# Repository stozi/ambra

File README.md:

# Ambra
A [Kalmar](https://github.com/aroum/kalmar)/[A. Dux](https://github.com/tapioki/cephalopoda/tree/main/Architeuthis%20dux)-based 34-key split ortho keyboard. [ZMK shield](https://github.com/stozi/zmk-keyboard-ambra)

### Included from Kalmar

- power switch
- reset button
- solder jumpers to mount the MCU the same way on both sides
- perforations on the tab for the connector between the right & left boards

### Changes from Kalmar

- thumb keys mount at 90° with pogo pins and 3D-printed magnet brackets
- besides Kailh Choc, support for Gateron KS-33, both hotswap only
- JST PH battery connector
- Switched the TRRS jack to the same pogo pin connector used for the thumb keys to prevent shorting (VCC/power is the middle pin so mounting one side backwards won't cause damage)
- ground plane for some ESD protection, new pinout

If you don't need fold-down packability or can't get the magnets, you can run a 9mm or longer M2 bolt through both brackets. However, any fall will then be more likely to cause damage.

Consider putting a non-conductive coating between the JST connector's mount points and the battery. Remove remnants of perforations on the thumb-key board before attaching the bracket. Personally, I solder the top-side jumpers to mount the MCUs component-side up so I can see the LEDs, and keep them safe under a case handcrafted from plumbing silicone.

Passed basic testing.

## BOM

Item     | Qty   | Notes 
----------|-------|-------
[SuperMini NRF52840 MCU](https://www.aliexpress.com/item/1005008099333183.html) | 2 | inc. sockets. Alternatively, ProMicro/Elite-C for a wired build
[Kailh Choc V1](https://a.aliexpress.com/_EGNqHgc) | 34 | key switches. Alternatively, [Gateron KS-33](https://a.aliexpress.com/_EuUuYVU)
[Choc hotswap sockets](https://a.aliexpress.com/_Eu2JK5E) | 34 | Alternatively, [Gateron KS-33 hotswap sockets](https://a.aliexpress.com/_EGlN42e)
[Keycaps](https://a.aliexpress.com/_EGNqLfE) | 34 | 1U. If using KS-33 switches, STL files are provided to print your own 'MX stem, Choc-1U-spaced' caps
[Magnets](https://a.aliexpress.com/_EGMQ442) | 2 | D6×3mm annular cylinder
[RTLECS MG03254 3-pin](https://a.aliexpress.com/_Ev5QIZa) | 2 straight m, 2 90° f | magnetic pogo-pin connectors
[MSK-12CO2](https://aliexpress.ru/item/1005001398386692.html) | 2 | power switch
[SMD button 3×4×2](https://aliexpress.ru/item/1005003812819985.html) | 2 | reset switch
[301230 li-po](https://aliexpress.ru/item/32732458079.html) | 2 | battery
[JST PH right-angle 2-pin](https://www.aliexpress.com/item/1005008131930144.html) | 2 | battery connector
[JST wire](https://www.aliexpress.com/item/1005001649158434.html) | 2 | solder & shrink tube to battery wires, no crimping needed, or [battery already with connector](https://a.aliexpress.com/_EJkhjGm) 
[M3 machine screws, 3mm](https://www.aliexpress.com/item/1005006662972635.html) | 2 | flathead, couples with magnet
[M3 thin hex nuts](https://a.aliexpress.com/_EvCkuwM) | 2 |
[M2 tapered head machine screws, 7mm](https://a.aliexpress.com/_EzeQ9lA) | 2 | holds magnet
[M2 flat head machine screws, 8mm](https://www.aliexpress.com/item/1005006662972635.html) | 6 | for brackets
[M2 thin hex nuts](https://a.aliexpress.com/_EvCkuwM) | 8 |
OPTIONAL: [RTLECS MG03254 cable](https://www.aliexpress.com/item/1005007988032729.html) and extra RTLECS 90° female connectors as listed above | 2 of each | For a wired build: cut, solder and shrink-tube the two wires together

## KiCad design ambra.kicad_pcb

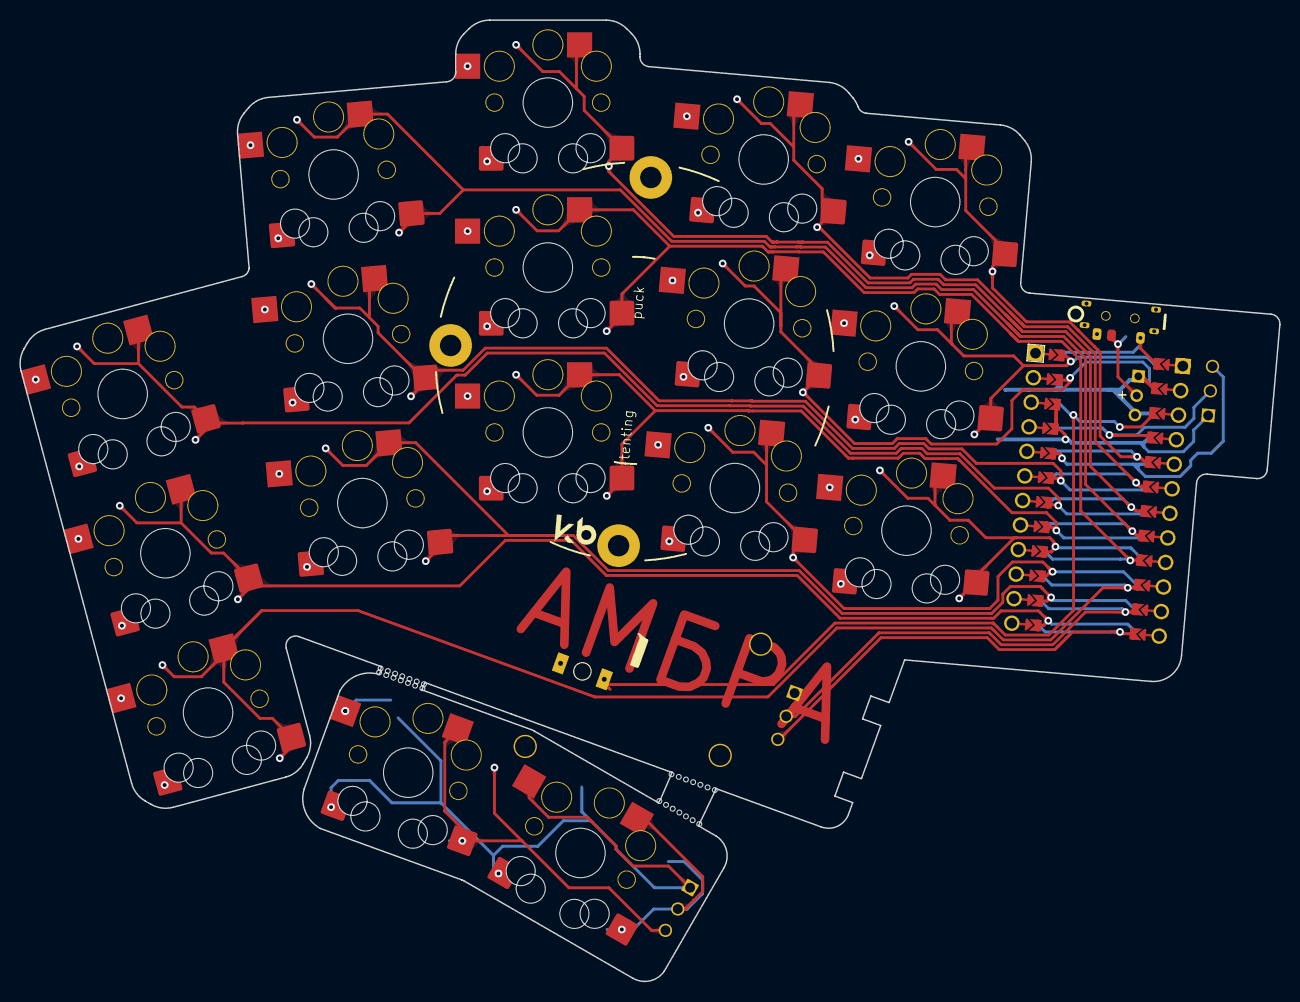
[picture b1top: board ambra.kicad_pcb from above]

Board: 2 copper layers, 129.8 x 99.1 mm, 25 parts (1 on the bottom side), 21 nets.

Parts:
BT3, BT3#2, BT3#3, BT3#4: Breakaway Tabs; Breakaway_Tabs
H1: Hole; HOLE
RSW1: SW_PUSH; reset-SW_3x4x2_2legs_x2
SW1: SW_SPDT; switch_MSK-12C02_smd_x2_topor
SWr1c1, SWr1c2, SWr1c3, SWr1c4, SWr1c5, SWr2c1, SWr2c2, SWr2c3, SWr2c4, SWr2c5, SWr3c1, SWr3c2, SWr3c3, SWr3c4, SWr3c5, SWr4c1, SWr4c2: SW_PUSH; Choc-and-KS33-Hotswap-Choc-1U
U1: ProMicro_r; ProMicro_duplex_clean

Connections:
GND: RSW1.2, SWr1c1.1, SWr1c1.2, SWr1c2.1, SWr1c2.2, SWr1c3.1, SWr1c3.2, SWr1c4.1, SWr1c4.2, SWr1c5.1, SWr1c5.2, SWr2c1.1, SWr2c1.2, SWr2c2.1, SWr2c2.2, SWr2c3.1, SWr2c3.2, SWr2c4.1, SWr2c4.2, SWr2c5.1, SWr2c5.2, SWr3c1.1, SWr3c1.2, SWr3c2.1, SWr3c2.2, SWr3c3.1, SWr3c3.2, SWr3c4.1, SWr3c4.2, SWr3c5.1, SWr3c5.2, U1.3 (GND), U1.4 (GND), U1.23 (GND)
GND2: SWr4c1.1, SWr4c1.2, SWr4c2.1, SWr4c2.2
VBAT: SW1.1 (A), U1.24 (RAW)
db1: SWr4c1.1, SWr4c1.2
db2: SWr4c2.1, SWr4c2.2
r1c1: SWr1c1.1, SWr1c1.2, U1.20 (A3/F4)
r1c2: SWr1c2.1, SWr1c2.2, U1.19 (A2/F5)
r1c3: SWr1c3.1, SWr1c3.2, U1.18 (A1/F6)
r1c4: SWr1c4.1, SWr1c4.2, U1.17 (A0/F7)
r1c5: SWr1c5.1, SWr1c5.2, U1.7 (D4/4)
r2c1: SWr2c1.1, SWr2c1.2, U1.1 (D3/TX0)
r2c2: SWr2c2.1, SWr2c2.2, U1.2 (D2/RX1)
r2c3: SWr2c3.1, SWr2c3.2, U1.16 (15/B1)
r2c4: SWr2c4.1, SWr2c4.2, U1.6 (SCL/D0/3)
r2c5: SWr2c5.1, SWr2c5.2, U1.12 (B5/9)
r3c1: SWr3c1.1, SWr3c1.2, U1.9 (D7/6)
r3c2: SWr3c2.1, SWr3c2.2, U1.10 (E6/7)
r3c3: SWr3c3.1, SWr3c3.2, U1.8 (C6/5)
r3c4: SWr3c4.1, SWr3c4.2, U1.11 (B4/8)
r3c5: SWr3c5.1, SWr3c5.2, U1.15 (14/B3)
reset: RSW1.1, U1.22 (RST)

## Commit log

2025-02-19 Update LICENSE
2025-04-30 Rename IMG_20250501_002447.jpg to prototype.jpg
